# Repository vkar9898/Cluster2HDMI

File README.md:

# Cluster2HDMI
A project that converts a 7" screen from a car dashboard to a standalone monitor.

## Why I made this

This screen comes from an Audi Q7 dashboard. Prior to this project, I was able to control the entire dashboard via CAN. After that, I wanted to control the LCD entirely independently, and use it as a standalone monitor. I have always found it interesting to reverse engineering things, so I believed this project would be a great start, and so far it has.

## What it does

This is a standalone monitor, so it can display graphics or what not connected directly to your PC.

## How it works

A HDMI cable will be plugged into the case, it will function as a secondary monitor, converting HDMI to Parallel RGB on the PCB, via a TFP401 microchip, and sending a  SPI sequence from a Pico 2 to the panel.

## Reverse engineering the panel

Originally, I had tried to search for datasheets available for my panel, but couldn't find any. This meant I had to reverse engineer it myself entirely. I began by connecting the dashboard's ribbon to one FFC breakout board and the panel's flex to another, with jumper wires between them, so I could probe every pin for continuity and voltage with a multimeter while the panel was running. Many problems were met here, more in the [journal](JOURNAL.md).

### Pin map (45-pin, 0.5 mm FPC)

Numbers are the breakout board labels.

| Label | Function | Notes |
|---|---|---|
| 1, 2, 13, 22, 31, 33, 37, 44, 45 | Ground | |
| 3 | Unknown | 1.5 kΩ pull-down to ground |
| 4, 38 | Power in | 3.3V |
| 5–12 | Blue B0–B7 | 5 = smallest bit |
| 14–21 | Green G0–G7 | 14 = smallest bit |
| 23–30 | Red R0–R7 | 23 = smallest bit |
| 32 | PCLK | Pixel clock |
| 34 | HSYNC | |
| 35 | VSYNC | |
| 36 | DE | Data enable |
| 39, 43 | Not connected | Unknown |
| 40 | SPI data (MOSI) | Setup commands |
| 41 | SPI chip select | Active low |
| 42 | SPI clock | |

### Video timing (measured from the cluster)

| | Value |
|---|---|
| Resolution | 800 × 480 |
| Pixel clock | ~26.8 MHz (cluster), 25 MHz (Pico) |
| Horizontal | HSYNC 10 px, back porch 6 px, active 800 px, front porch 106 px, total 922 px |
| Vertical | active 480 lines, front porch 8, VSYNC 4, back porch 8, total 500 lines |
| Refresh rate | ~58 Hz (cluster), ~54 Hz (Pico) |
| Sync polarity | HSYNC and VSYNC active low, DE active high |

### SPI setup sequence

The sequence that the cluster sends to the panel to 'stay alive', or a gamma/brightness setting. It consists of 3 wires at ~500 kHz. It starts ~25 ms after video starts, and without it the panel stays black.

| Step | Bytes (hex) | Delay after |
|---|---|---|
| 1 | 1B 50 00 | 2.15 ms |
| 2 | 1D 5C 00 | 2.15 ms |
| 3 | 10 00 | 2.15 ms |
| 4 | 08 80 | ~125.6 ms |
| 5 | 14 80 | |

The cluster repeats the whole set every ~545.6 ms. What each register does is unknown.

## Current status

The design is finished, including the PCB, case, and firmware, and is waiting on funding to order and build.

## Wiring (current test setup)

Breakout A = panel side, Breakout B = cluster side.

### Timing and SPI

| Pico 2 | Breakout A | Signal |
|---|---|---|
| GP0 | 32 | PCLK |
| GP1 | 36 | DE |
| GP2 | 34 | HSYNC |
| GP27 | 35 | VSYNC |
| GP28 | — | Not connected (used internally by the Pico) |
| GP21 | 42 | SPI clock |
| GP22 | 40 | SPI data (MOSI) |
| GP26 | 41 | SPI chip select |
| GND | Ground rail | Ground |

### Colour data (top 6 bits of each colour)

| Colour | Bit | Breakout A | Pico 2 |
|---|---|---|---|
| Blue | B2 | 7 | GP5 |
| Blue | B3 | 8 | GP6 |
| Blue | B4 | 9 | GP7 |
| Blue | B5 | 10 | GP8 |
| Blue | B6 | 11 | GP3 |
| Blue | B7 | 12 | GP9 |
| Green | G2 | 16 | GP12 |
| Green | G3 | 17 | GP13 |
| Green | G4 | 18 | GP14 |
| Green | G5 | 19 | GP4 |
| Green | G6 | 20 | GP15 |
| Green | G7 | 21 | GP10 |
| Red | R2 | 25 | GP18 |
| Red | R3 | 26 | GP19 |
| Red | R4 | 27 | GP20 |
| Red | R5 | 28 | GP11 |
| Red | R6 | 29 | GP16 |
| Red | R7 | 30 | GP17 |

### Resistors to ground

| Breakout A | Resistor | Why |
|---|---|---|
| 3 | 1 kΩ | 1.5 kΩ pull-down |
| 5, 6 | 2.2 kΩ each | Blue B0–B1 held low (unused) |
| 14, 15 | 2.2 kΩ each | Green G0–G1 held low (unused) |
| 23, 24 | 2.2 kΩ each | Red R0–R1 held low (unused) |

### Cluster to panel (breakout B → breakout A)

| Connection | Purpose |
|---|---|
| B4 → A4 | Panel power from the cluster |
| B38 → A38 | Panel power from the cluster |
| A1, 2, 13, 22, 31, 33, 37, 44, 45 → ground rail | Panel grounds |
| B1, 22, 44 → ground rail | Cluster ground |
| A39, A43 | Left unconnected |
| 10-pin backlight ribbon | Stays plugged into the cluster |

Power order: cluster on first, then plug in the Pico.

## Hardware

The TFP401 converts HDMI to parallel RGB, and the SPI sequence comes from the Pico
### Video path
HDMI input, into the TFP401 chip, outputting TTL/Parallel RGB, and connects to the 45-pin connector
### Power
12V input, converted to 5V, 3.3V, and 22.5V, via buck converters and boost converters, with a resettable fuse (F2)
### Backlight
Driven by the 22.5V, with 3 LED strings that return through a 20mA constant-current chip. A MOSFET then switches them with PWM from the Pico for brightness.
### Pico 2
SPI sequence on pins 4-6 of the 45-pin connector, the backlight, and the EDID.
### EDID
A memory chip (AT24C02 EEPROM) on the HDMI's DDC lines. The Pico writes it through a level shifter, and it tells the PC the screens resolution, and monitor name.

## Firmware

Currently, the Pico code is MicroPython, written and run through Thonny. It generates the timing signals (PCLK, HSYNC, VSYNC, DE) using the Pico's PIO hardware, sends the SPI  sequence, and controls the red, green and blue bits. The test firmware was written with help from Claude (AI), and is able to send the SPI sequence, turn backlight on, and write the EDID with the correct resolution and monitor name. Code can be found [here](Firmware), the file is cluster2hdmi_main.py. It is still, however, untested, as the PCB hasn't been ordered yet.

## How to flash

1. Holding BOOTSEL, plug in your Pico, and drag the [MicroPython .uf2 file](https://micropython.org/download/RPI_PICO2/) onto the drive that appears.
2. Open Thonny and choose the Pico as the interpreter, before saving the [firmware](Firmware) file onto the Pico as "main.py". After this, it'll run automatically on power-up. 
3. Turn on the Pico 2, and the software should run!

## Known issues

* Pins 3, 39 and 43's functions are unknown
* Exactly what each SPI register does is unknown, but easily replicable
* Unknown whether the panel needs SPI commands repeated
* Pico test driver uses 6 bits per colour, not 8, and can only show solid colours
* Loose wiring can cause unexpected disconnections

## Building one yourself

1. Ordering all required parts: BOM, + specific JLC parts. Gerbers available in KiCad/Cluster2HDMI/gerbers.zip, and JLC BOM and CPL are in KiCad/Fabrication
2. Soldering the 20pin female headers for the Pico 2 is required, as JLC is out of stock of them
3. Printing the case, case_shell.stl and case_back_cover.stl
4. Putting it together: PCB screws onto 2 posts on the back cover with M2x8 screws, 45-pin and 10-pin ribbons connect to the board, Pico to its socket, and finally, the cover going into the shell, with 2 M2 x 30 screws going through the cover into the panel's top holes
5. Powering it up, the Pico writes the EDID, so the cable needs unplugging and replugging once before the PC sees the screen properly.

## Bill of Materials

All prices in USD (AliExpress prices converted from AUD). Full list with notes: [bom.csv](bom.csv). Every part on the PCB (with LCSC numbers) is in [KiCad/Fabrication/Cluster2HDMI_BOM_JLC_v2.csv](KiCad/Fabrication/Cluster2HDMI_BOM_JLC_v2.csv).

| Section | Item | Designators / use | Part # / search term | Supplier | Qty | Unit price (USD) | Line total (USD) | Price status | Link | Notes |
|---|---|---|---|---|---|---|---|---|---|---|
| PCB + assembly | Multi-Cluster-Control PCB, 5 boards, 2 assembled (Economic PCBA, 1 oz, top side) | Whole board, all JLC-placed parts | Gerbers + BOM + CPL from Fabrication Toolkit | JLCPCB | 1 | $65.70 | $65.70 | Quoted | [link](https://jlcpcb.com) | PCB $9.80 + PCBA $55.90 |
| PCB + assembly | JLCPCB coupon |  |  | JLCPCB | 1 | -$10.00 | -$10.00 | Quoted |  |  |
| PCB + assembly | Keystone 3568 mini-blade fuse holder (idle parts) | F1, F2 (2 boards) | C5249699 | JLCPCB parts cart | 4 | $1.21 | $4.84 | Quoted | [link](https://jlcpcb.com/partdetail/C5249699) | Idle parts |
| Board parts not assembled by JLC | Cluster plug, 10-pin 3.81 mm screw (KANGNEX WJ15EDGK-3.81-10P-14-00A) | CN1-CN3, 2 per header | C26865 | LCSC | 6 | $0.8112 | $4.87 | Quoted | [link](https://www.lcsc.com/product-detail/C26865.html) |  |
| Board parts not assembled by JLC | Cluster plug, 4-pin 3.81 mm screw (KANGNEX WJ15EDGK-3.81-04P-14-00A) | CN4, 2 per header | C7244 (min order 5) | LCSC | 5 | $0.3082 | $1.54 | Quoted | [link](https://www.lcsc.com/product-detail/C7244.html) | Min order 5 |
| Board parts not assembled by JLC | 5-way screw terminal, 5.08 mm (Phoenix MKDS 1,5/5-5,08, 1715750) | J15 | C6042418 | LCSC | 2 | $1.2721 | $2.54 | Quoted | [link](https://www.lcsc.com/product-detail/C6042418.html) | 1 spare |
| Board parts not assembled by JLC | 1x14 female header 2.54 mm | J11 (VID6606 adapter), 2 per board | C2905420 (min order 5) | LCSC | 5 | $0.1580 | $0.79 | Quoted | [link](https://www.lcsc.com/product-detail/C2905420.html) | Min order 5 |
| Modules and chips | VID6606 stepper driver, SOP-28 (5 pcs) | X-90 speedo stepper driver | VID6606 | AliExpress | 1 | $4.61 | $4.61 | Quoted | [link](https://www.aliexpress.com/item/1005007323081013.html) |  |
| Modules and chips | SOP-28 to DIP-28 adapter boards (10 pcs) | Carrier for the VID6606 in J11 | SOP28 to DIP28 | AliExpress | 1 | $1.73 | $1.73 | Quoted | [link](https://www.aliexpress.com/item/32909339596.html) | 15.24 mm DIP width |
| Modules and chips | X27.168 gauge stepper motor | X-90 speedo + 1 spare | X27.168 | AliExpress | 2 | $2.35 | $4.70 | Quoted | [link](https://www.aliexpress.com/item/1005006620561935.html) |  |
| Modules and chips | PCA9685 16-ch PWM module | J5/J6 (gauge PWM) | PCA9685 | AliExpress | 1 | $3.79 | $3.79 | Quoted | [link](https://www.aliexpress.com/item/1005005670283526.html) |  |
| Modules and chips | MCP2515 CAN module, TJA1050, 8 MHz | Second CAN module | MCP2515 TJA1050 | AliExpress | 1 | $0.92 | $0.92 | Quoted | [link](https://www.aliexpress.com/item/1005010199935143.html) | 8 MHz crystal |
| Modules and chips | MP1584EN adjustable buck module (5 pcs) | M5 (5.0 V), M6 (3.6 V) | MP1584EN | AliExpress | 1 | $3.15 | $3.15 | Quoted | [link](https://www.aliexpress.com/item/1005007653423578.html) | Set voltage before soldering |
| Modules and chips | MT3608 boost module | M7 (24 V) | MT3608 / 1PCS | AliExpress | 1 | $2.38 | $2.38 | Quoted | [link](https://www.aliexpress.com/item/1005011548818999.html) | Set to 24 V |
| Wiring | 20-core 20 AWG RVV sheathed cable, 2 m | 4 cluster cables x 0.5 m | RVV 20 core 20 AWG, 2 m option | AliExpress | 1 | $18.73 | $18.73 | Quoted | [link](https://www.aliexpress.com/item/1005004200589656.html) |  |
| Wiring | Dupont jumpers, female-female, 10 cm, 40 pcs | PCA9685, MCP2515 x2, light sensor | Dupont F-F 10 cm | AliExpress | 1 | $0.99 | $0.99 | Quoted | [link](https://www.aliexpress.com/item/1005009372155336.html) |  |
| Power | 12 V 4 A plug pack, 5.5 x 2.1 mm, AU plug | J1, J2 | 4A/12 V/AU Plug | AliExpress | 2 | $4.19 | $8.38 | Quoted | [link](https://www.aliexpress.com/item/1005013455261196.html) | Centre-positive |
| Power | SCA mini blade fuse 5 A, 6 pack | F1, F2 + spares | 726696 | Supercheap Auto | 1 | $2.81 | $2.81 | Quoted | [link](https://www.supercheapauto.com.au/p/sca-sca-automotive-fuses-mini-blade-5-amp-6-pack/726696.html) | Click & collect |
| Lighting | T10 (W5W) LED wedge bulbs, 6500K white, 10 pack | Cluster illumination | ASIN B0HGLD6KBJ | Amazon AU | 1 | $6.33 | $6.33 | Quoted | [link](https://www.amazon.com.au/dp/B0HGLD6KBJ) | Polarised |
| Mounting | M3 x 16 mm pan head screws + M3 nuts | Board to support, 4 holes | M3 x 16 machine screws + nuts | Bunnings | 1 | $3.52 | $3.52 | Estimate |  |  |
| Discounts | AliExpress checkout discounts |  |  | AliExpress | 1 | -$4.34 | -$4.34 | Quoted |  |  |
| Already owned | ESP32 dev board (38-pin) | J3/J4 |  | Owned | 1 | $0.00 | $0.00 | Owned |  |  |
| Already owned | Light sensor module | J14 |  | Owned | 1 | $0.00 | $0.00 | Owned |  |  |
| Already owned | MCP2515 CAN module (first one) | J7 or J9 |  | Owned | 1 | $0.00 | $0.00 | Owned |  |  |
| Shipping | Shipping: DHL Express (PCB + assembly + idle parts) |  |  | JLCPCB | 1 | $18.11 | $18.11 | Quoted |  |  |
| Shipping | Shipping: Global Direct Standard Line |  |  | LCSC | 1 | $9.93 | $9.93 | Quoted |  |  |
| Shipping | Shipping: Handling fee |  |  | LCSC | 1 | $3.00 | $3.00 | Quoted |  | Waived over $15.55 merchandise |
| Shipping | Shipping: Dupont jumper store |  |  | AliExpress | 1 | $3.08 | $3.08 | Quoted |  |  |
| Shipping | Shipping: MCP2515 store |  |  | AliExpress | 1 | $2.27 | $2.27 | Quoted |  |  |
| Shipping | Shipping: All other items |  |  | AliExpress | 1 | $0.00 | $0.00 | Quoted |  | Free shipping |
| Shipping | Shipping: Click & collect |  |  | Supercheap Auto | 1 | $0.00 | $0.00 | Quoted |  |  |
| Shipping | Shipping: Standard delivery (T10 bulbs) |  |  | Amazon AU | 1 | $0.00 | $0.00 | Estimate |  | Free over AU$49 |
 
**Total: $164.37** (parts $127.98 + shipping $36.39)

## Credits & references

- [LogicAnalyzer by gusmanb](https://github.com/gusmanb/logicanalyzer)
- [Adafruit TFP401 HDMI/DVI decoder](https://www.adafruit.com/product/2219)
- Claude (AI): helped write the test firmware, decode the logic analyser captures, routing the PCB, and aided with designing the case

## Licence

MIT, see [LICENSE](LICENSE).

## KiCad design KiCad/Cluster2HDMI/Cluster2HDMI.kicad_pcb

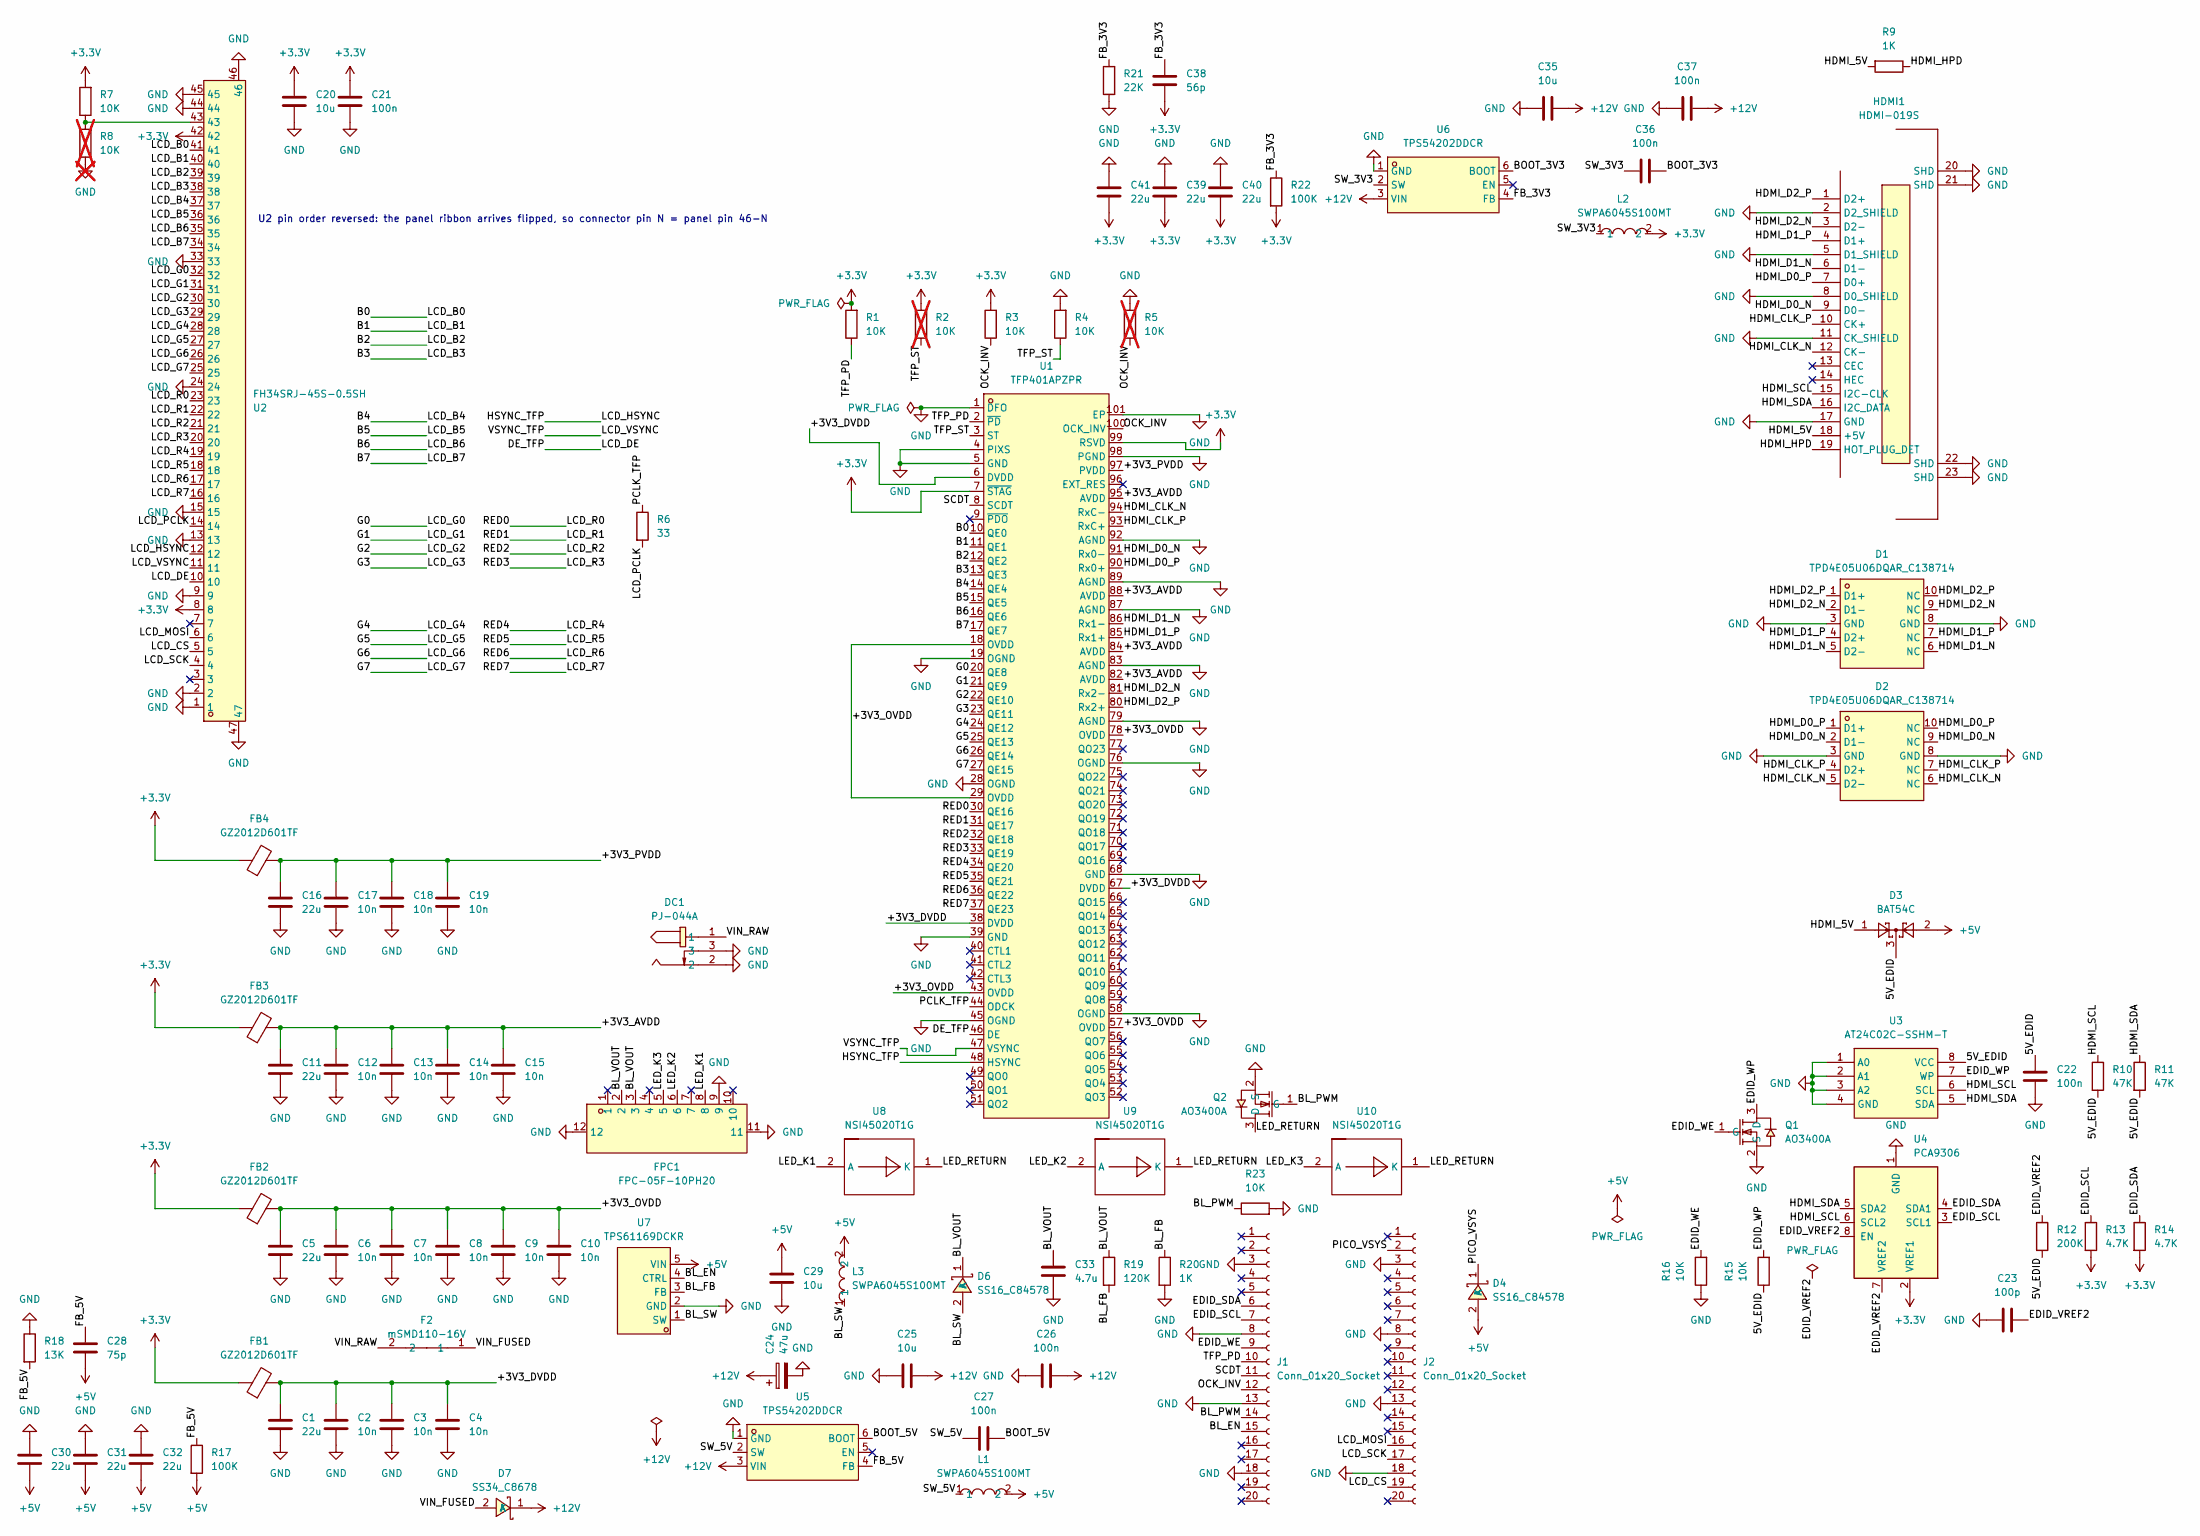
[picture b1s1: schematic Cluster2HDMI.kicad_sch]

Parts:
C1, C5, C11, C16, C30, C31, C32, C39, C40, C41: 22u; C_0805_2012Metric; LCSC Part C45783
C2, C3, C4, C6, C7, C8, C9, C10, C12, C13, C14, C15, C17, C18, C19: 10n; C_0603_1608Metric; LCSC Part C57112
C20, C25, C29, C35: 10u; C_0805_2012Metric; LCSC Part C15850
C21, C22, C26, C27, C36, C37: 100n; C_0603_1608Metric; LCSC Part C14663
C23: 100p; C_0603_1608Metric; LCSC Part C14858
C24: 47u; CP_Elec_6.3x5.4; LCSC Part C178505
C28: 75p; C_0603_1608Metric; LCSC Part C282074
C33: 4.7u; C_1206_3216Metric; LCSC Part C51205
C38: 56p; C_0603_1608Metric; LCSC Part C39148
D1, D2: TPD4E05U06DQAR_C138714; USON-10_L2.5-W1.0-P0.50-BL; MPN TPD4E05U06DQAR; LCSC Part C138714
D3: BAT54C; SOT-23; LCSC Part C37704
D4, D6: SS16_C84578; SMA_L4.4-W2.6-LS5.0-RD; MPN SS16; LCSC Part C84578
D7: SS34_C8678; SMA_L4.3-W2.6-LS5.2-RD; MPN SS34; LCSC Part C8678
DC1: PJ-044A; DC-IN-TH_PJ-044A; MPN PJ-044A; LCSC Part C3095965
F2: mSMD110-16V; F1812; MPN mSMD110-16V; LCSC Part C69691
FB1, FB2, FB3, FB4: GZ2012D601TF; L_0805_2012Metric; LCSC Part C1017
FPC1: FPC-05F-10PH20; FPC-SMD_10P-P0.50_XUNPU_FPC-05F-10PH20; MPN FPC-05F-10PH20; LCSC Part C2856798
HDMI1: HDMI-019S; HDMI-SMD_HDMI-019S; MPN HDMI-019S; LCSC Part C111617
J1, J2: Conn_01x20_Socket; PinSocket_1x20_P2.54mm_Vertical; LCSC Part C50984
L1, L2, L3: SWPA6045S100MT; IND-SMD_L6.0-W6.0_SWPA6045S; MPN SWPA6045S100MT; LCSC Part C79272
Q1, Q2: AO3400A; SOT-23-3_L2.9-W1.3-P1.90-LS2.4-BR; MPN AO3400A; LCSC Part C20917
R1, R3, R4, R7, R15, R16, R23: 10K; R_0603_1608Metric; LCSC Part C25804
R2, R5, R8: 10K; R_0603_1608Metric; LCSC Part C25804; not fitted
R6: 33; R_0603_1608Metric; LCSC Part C23140
R9, R20: 1K; R_0603_1608Metric; LCSC Part C21190
R10, R11: 47K; R_0603_1608Metric; LCSC Part C25819
R12: 200K; R_0603_1608Metric; LCSC Part C25811
R13, R14: 4.7K; R_0603_1608Metric; LCSC Part C23162
R17, R22: 100K; R_0603_1608Metric; LCSC Part C25803
R18: 13K; R_0603_1608Metric; LCSC Part C22797
R19: 120K; R_0603_1608Metric; LCSC Part C25808
R21: 22K; R_0603_1608Metric; LCSC Part C31850
U1: TFP401APZPR; HTQFP-100_L14.0-W14.0-P0.50-LS16.0-BL-EP6.2; MPN TFP401APZPR; LCSC Part C962083
U2: FH34SRJ-45S-0.5SH; FPC-SMD_45P-P0.50_FH34SRJ-45S-0.5SH-50; MPN FH34SRJ-45S-0.5SH(50); LCSC Part C3170034
U3: AT24C02C-SSHM-T; SOIC-8_L5.0-W4.0-P1.27-LS6.0-BL; MPN AT24C02C-SSHM-T; LCSC Part C6203
U4: PCA9306; SSOP-8_2.95x2.8mm_P0.65mm; LCSC Part C123752
U5, U6: TPS54202DDCR; SOT-23-6_L2.9-W1.6-P0.95-LS2.8-BL; MPN TPS54202DDCR; LCSC Part C191884
U7: TPS61169DCKR; SC-70-5_L2.1-W1.3-P0.65-LS2.1-BR; MPN TPS61169DCKR; LCSC Part C71045
U8, U9, U10: NSI45020T1G; SOD-123F_L2.8-W1.8-LS3.7-RD; MPN NSI45020T1G; LCSC Part C129159

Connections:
+3.3V: C20.1, C21.1, C38.2, C39.1, C40.1, C41.1, FB1.1, FB2.1, FB3.1, FB4.1, L2.2, R1.2, R2.2, R3.2, R7.2, R13.2, R14.2, R22.2, U1.7 (~STAG), U1.99 (RSVD), U2.8, U2.42, U4.2 (VREF1)
+5V: C28.2, C29.1, C30.1, C31.1, C32.1, D3.2, D4.2 (A), L1.2, L3.2, R17.2, U7.5 (VIN)
+12V: C24.1, C25.2, C26.2, C35.2, C37.2, D7.1 (K), U5.3 (VIN), U6.3 (VIN)
/5V_EDID: C22.1, D3.3, R10.2, R11.2, R12.2, R15.1, U3.8 (VCC)
/+3V3_AVDD: C11.1, C12.1, C13.1, C14.1, C15.1, FB3.2, U1.82 (AVDD), U1.84 (AVDD), U1.88 (AVDD), U1.95 (AVDD)
/+3V3_DVDD: C1.1, C2.1, C3.1, C4.1, FB1.2, U1.6 (DVDD), U1.38 (DVDD), U1.67 (DVDD)
/+3V3_OVDD: C5.1, C6.1, C7.1, C8.1, C9.1, C10.1, FB2.2, U1.18 (OVDD), U1.29 (OVDD), U1.43 (OVDD), U1.57 (OVDD), U1.78 (OVDD)
/+3V3_PVDD: C16.1, C17.1, C18.1, C19.1, FB4.2, U1.97 (PVDD)
/B0: U1.10 (QE0), U2.41
/B1: U1.11 (QE1), U2.40
/B2: U1.12 (QE2), U2.39
/B3: U1.13 (QE3), U2.38
/B4: U1.14 (QE4), U2.37
/B5: U1.15 (QE5), U2.36
/B6: U1.16 (QE6), U2.35
/B7: U1.17 (QE7), U2.34
/BL_EN: J1.15, U7.4 (CTRL)
/BL_FB: R19.2, R20.1, U7.3 (FB)
/BL_PWM: J1.14, Q2.1 (G), R23.1
/BL_SW: D6.2 (A), L3.1, U7.1 (SW)
/BL_VOUT: C33.1, D6.1 (K), FPC1.2, FPC1.3, R19.1
/BOOT_3V3: C36.2, U6.6 (BOOT)
/BOOT_5V: C27.2, U5.6 (BOOT)
/DE_TFP: U1.46 (DE), U2.10
/EDID_SCL: J1.7, R13.1, U4.3 (SCL1)
/EDID_SDA: J1.6, R14.1, U4.4 (SDA1)
/EDID_VREF2: C23.2, R12.1, U4.7 (VREF2), U4.8 (EN)
/EDID_WE: J1.9, Q1.1 (G), R16.2
/EDID_WP: Q1.3 (D), R15.2, U3.7 (WP)
/FB_3V3: C38.1, R21.2, R22.1, U6.4 (FB)
/FB_5V: C28.1, R17.1, R18.2, U5.4 (FB)
/G0: U1.20 (QE8), U2.32
/G1: U1.21 (QE9), U2.31
/G2: U1.22 (QE10), U2.30
/G3: U1.23 (QE11), U2.29
/G4: U1.24 (QE12), U2.28
/G5: U1.25 (QE13), U2.27
/G6: U1.26 (QE14), U2.26
/G7: U1.27 (QE15), U2.25
/HDMI_5V: D3.1, HDMI1.18 (+5V), R9.2
/HDMI_CLK_N: D2.5 (D2-), D2.6 (NC), HDMI1.12 (CK-), U1.94 (RxC−)
/HDMI_CLK_P: D2.4 (D2+), D2.7 (NC), HDMI1.10 (CK+), U1.93 (RxC+)
/HDMI_D0_N: D2.2 (D1-), D2.9 (NC), HDMI1.9 (D0-), U1.91 (Rx0−)
/HDMI_D0_P: D2.1 (D1+), D2.10 (NC), HDMI1.7 (D0+), U1.90 (Rx0+)
/HDMI_D1_N: D1.5 (D2-), D1.6 (NC), HDMI1.6 (D1-), U1.86 (Rx1−)
/HDMI_D1_P: D1.4 (D2+), D1.7 (NC), HDMI1.4 (D1+), U1.85 (Rx1+)
/HDMI_D2_N: D1.2 (D1-), D1.9 (NC), HDMI1.3 (D2-), U1.81 (Rx2−)
/HDMI_D2_P: D1.1 (D1+), D1.10 (NC), HDMI1.1 (D2+), U1.80 (Rx2+)
/HDMI_HPD: HDMI1.19 (HOT_PLUG_DET), R9.1
/HDMI_SCL: HDMI1.15 (I2C-CLK), R10.1, U3.6 (SCL), U4.6 (SCL2)
/HDMI_SDA: HDMI1.16 (I2C_DATA), R11.1, U3.5 (SDA), U4.5 (SDA2)
/HSYNC_TFP: U1.48 (HSYNC), U2.12
/LCD_CS: J2.19, U2.5
/LCD_MOSI: J2.16, U2.6
/LCD_PCLK: R6.2, U2.14
/LCD_R0: U1.30 (QE16), U2.23
/LCD_R1: U1.31 (QE17), U2.22
/LCD_R2: U1.32 (QE18), U2.21
/LCD_R3: U1.33 (QE19), U2.20
/LCD_R4: U1.34 (QE20), U2.19
/LCD_R5: U1.35 (QE21), U2.18
/LCD_R6: U1.36 (QE22), U2.17
/LCD_R7: U1.37 (QE23), U2.16
/LCD_SCK: J2.17, U2.4
/LCD_VSYNC: U1.47 (VSYNC), U2.11
/LED_K1: FPC1.8, U8.2 (A)
/LED_K2: FPC1.6, U9.2 (A)
/LED_K3: FPC1.5, U10.2 (A)
/LED_RETURN: Q2.3 (D), U8.1 (K), U9.1 (K), U10.1 (K)
/OCK_INV: J1.12, R3.1, R5.1, U1.100 (OCK_INV)
/PCLK_TFP: R6.1, U1.44 (ODCK)
/PICO_VSYS: D4.1 (K), J2.2
/SCDT: J1.11, U1.8 (SCDT)
/SW_3V3: C36.1, L2.1, U6.2 (SW)
/SW_5V: C27.1, L1.1, U5.2 (SW)
/TFP_PD: J1.10, R1.1, U1.2 (~PD)
/TFP_ST: R2.1, R4.1, U1.3 (ST)
/VIN_FUSED: D7.2 (A), F2.1
/VIN_RAW: DC1.1, F2.2
GND: C1.2, C2.2, C3.2, C4.2, C5.2, C6.2, C7.2, C8.2, C9.2, C10.2, C11.2, C12.2, C13.2, C14.2, C15.2, C16.2, C17.2, C18.2, C19.2, C20.2, C21.2, C22.2, C23.1, C24.2, C25.1, C26.1, C29.2, C30.2, C31.2, C32.2, C33.2, C35.1, C37.1, C39.2, C40.2, C41.2, D1.3 (GND), D1.8 (GND), D2.3 (GND), D2.8 (GND), DC1.2, DC1.3, FPC1.9, FPC1.11, FPC1.12, HDMI1.2 (D2_SHIELD), HDMI1.5 (D1_SHIELD), HDMI1.8 (D0_SHIELD), HDMI1.11 (CK_SHIELD), HDMI1.17 (GND), HDMI1.20 (SHD), HDMI1.21 (SHD), HDMI1.22 (SHD), HDMI1.23 (SHD), J1.3, J1.8, J1.13, J1.18, J2.3, J2.8, J2.13, J2.18, Q1.2 (S), Q2.2 (S), R4.2, R5.2, R8.1, R16.1, R18.1, R20.2, R21.1, R23.2, U1.1 (DFO), U1.4 (PIXS), U1.5 (GND), U1.19 (OGND), U1.28 (OGND), U1.39 (GND), U1.45 (OGND), U1.58 (OGND), U1.68 (GND), U1.76 (OGND), U1.79 (AGND), U1.83 (AGND), U1.87 (AGND), U1.89 (AGND), U1.92 (AGND), U1.98 (PGND), U1.101 (EP), U2.1, U2.2, U2.9, U2.13, U2.15, U2.24, U2.33, U2.44, U2.45, U2.46, U2.47, U3.1 (A0), U3.2 (A1), U3.3 (A2), U3.4 (GND), U4.1 (GND), U5.1 (GND), U6.1 (GND), U7.2 (GND); also elsewhere on the board
unnamed: R7.1, R8.2, U2.43

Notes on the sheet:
U2 pin order reversed: the panel ribbon arrives flipped, so connector pin N = panel pin 46-N

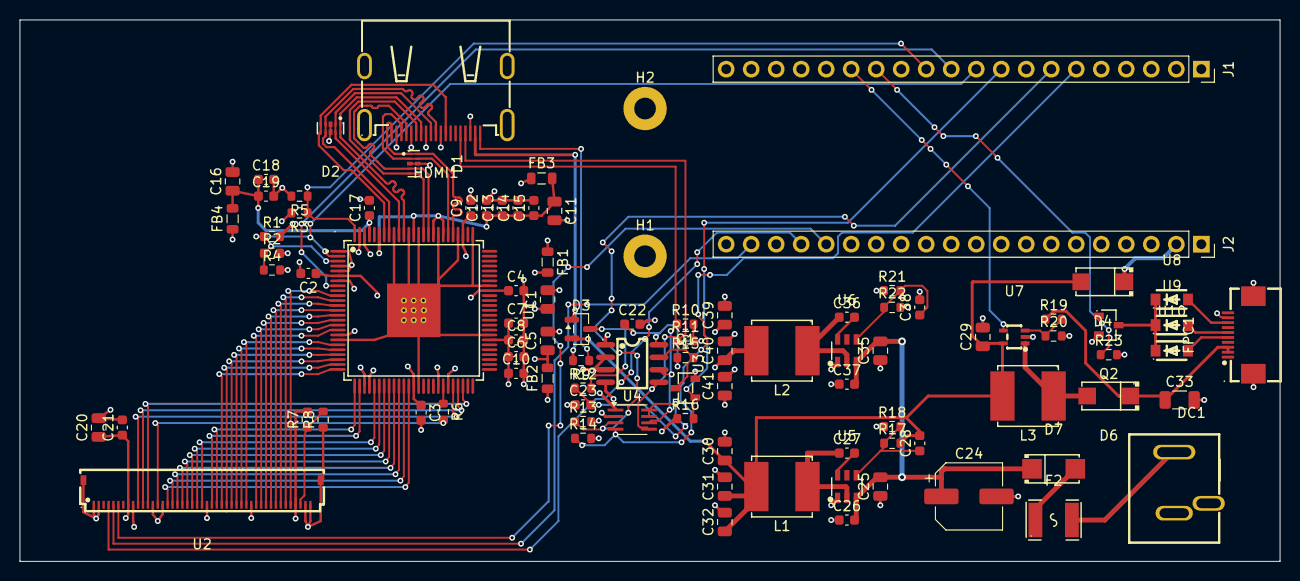
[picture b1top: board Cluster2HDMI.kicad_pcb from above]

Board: 4 copper layers, 128.0 x 55.0 mm, 96 parts (0 on the bottom side), 81 nets.

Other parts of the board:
H1, H2: MountingHole_2.2mm_M2_Pad

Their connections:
GND: H1.1, H2.1; also elsewhere on the board

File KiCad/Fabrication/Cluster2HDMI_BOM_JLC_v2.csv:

Comment,Designator,Footprint,LCSC Part #
22u,"C1,C5,C11,C16,C30,C31,C32,C39,C40,C41",C_0805_2012Metric,C45783
10n,"C2,C3,C4,C6,C7,C8,C9,C10,C12,C13,C14,C15,C17,C18,C19",C_0603_1608Metric,C57112
10u,"C20,C25,C29,C35",C_0805_2012Metric,C15850
100n,"C21,C22,C26,C27,C36,C37",C_0603_1608Metric,C14663
100p,C23,C_0603_1608Metric,C14858
47u,C24,CP_Elec_6.3x5.4,C7469965
75p,C28,C_0603_1608Metric,C282074
4.7u,C33,C_1206_3216Metric,C51205
56p,C38,C_0603_1608Metric,C39148
TPD4E05U06DQAR_C138714,"D1,D2",USON-10_L2.5-W1.0-P0.50-BL,C138714
BAT54C,D3,SOT-23,C37704
SS16_C84578,"D4,D6",SMA_L4.4-W2.6-LS5.0-RD,C84578
SS34_C8678,D7,SMA_L4.3-W2.6-LS5.2-RD,C8678
PJ-044A,DC1,DC-IN-TH_PJ-044A,C3095965
mSMD110-16V,F2,F1812,C69691
GZ2012D601TF,"FB1,FB2,FB3,FB4",L_0805_2012Metric,C1017
FPC-05F-10PH20,FPC1,FPC-SMD_10P-P0.50_XUNPU_FPC-05F-10PH20,C2856798
HDMI-019S,HDMI1,HDMI-SMD_HDMI-019S,C111617
SWPA6045S100MT,"L1,L2,L3",IND-SMD_L6.0-W6.0_SWPA6045S,C79272
AO3400A,"Q1,Q2",SOT-23-3_L2.9-W1.3-P1.90-LS2.4-BR,C20917
10K,"R1,R3,R4,R7,R15,R16,R23",R_0603_1608Metric,C25804
33,R6,R_0603_1608Metric,C23140
1K,"R9,R20",R_0603_1608Metric,C21190
47K,"R10,R11",R_0603_1608Metric,C25819
200K,R12,R_0603_1608Metric,C25811
4.7K,"R13,R14",R_0603_1608Metric,C23162
100K,"R17,R22",R_0603_1608Metric,C25803
13K,R18,R_0603_1608Metric,C22797
120K,R19,R_0603_1608Metric,C25808
22K,R21,R_0603_1608Metric,C31850
TFP401APZPR,U1,HTQFP-100_L14.0-W14.0-P0.50-LS16.0-BL-EP6.2,C962083
FH34SRJ-45S-0.5SH,U2,FPC-SMD_45P-P0.50_FH34SRJ-45S-0.5SH-50,C3170034
AT24C02C-SSHM-T,U3,SOIC-8_L5.0-W4.0-P1.27-LS6.0-BL,C6203
PCA9306,U4,SSOP-8_2.95x2.8mm_P0.65mm,C123752
TPS54202DDCR,"U5,U6",SOT-23-6_L2.9-W1.6-P0.95-LS2.8-BL,C191884
TPS61169DCKR,U7,SC-70-5_L2.1-W1.3-P0.65-LS2.1-BR,C71045
NSI45020T1G,"U8,U9,U10",SOD-123F_L2.8-W1.8-LS3.7-RD,C129159

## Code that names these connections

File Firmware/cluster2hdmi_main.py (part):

# cluster2hdmi_main.py
#
# Pin map 
#   GP4  (pin 6)   EDID_SDA  I2C0 SDA -> PCA9306 -> HDMI DDC / EEPROM
#   GP5  (pin 7)   EDID_SCL  I2C0 SCL
#   GP6  (pin 9)   EDID_WE   high = EEPROM write enabled (Q1 pulls WP low)
#   GP7  (pin 10)  TFP_PD    low = TFP401 powered down (R1 pull-up keeps it on)
#   GP8  (pin 11)  SCDT      input, high = TFP401 sees a valid HDMI/DVI signal
#   GP9  (pin 12)  OCK_INV   TFP401 pixel clock polarity (R3 pull-up = high). Left as input by default
#   GP10 (pin 14)  BL_PWM    Q2 gate, PWM = LED brightness (R23 pull-down = off)
#   GP11 (pin 15)  BL_EN     TPS61169 backlight boost enable
#   GP17 (pin 22)  LCD_CS    panel SPI chip select (active low)
#   GP18 (pin 24)  LCD_SCK   SPI0 SCK
#   GP19 (pin 25)  LCD_MOSI  SPI0 TX
#
# Shell commands:
#   brightness(0-100)   backlight(True/False)   status()
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
# pins
led = Pin("LED", Pin.OUT, value=0)
tfp_pd = Pin(7, Pin.OUT, value=1)                    # keep TFP401 on
scdt = Pin(8, Pin.IN)
ock = Pin(9, Pin.IN)                                 # leave to the pull-up
edid_we = Pin(6, Pin.OUT, value=0)                   # EEPROM write-protected
bl_en = Pin(11, Pin.OUT, value=0)
bl_pwm = PWM(Pin(10))
bl_pwm.freq(PWM_FREQ)
bl_pwm.duty_u16(0)
lcd_cs = Pin(17, Pin.OUT, value=1)

if USE_HW_SPI:
    spi = SPI(0, baudrate=500_000, polarity=0, phase=0, bits=8, firstbit=SPI.MSB,
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
    while True:
        now = time.ticks_ms()
        sig = scdt() == 1

        # video appeared: send the setup straight away, then backlight on
        if sig and not have_signal:
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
